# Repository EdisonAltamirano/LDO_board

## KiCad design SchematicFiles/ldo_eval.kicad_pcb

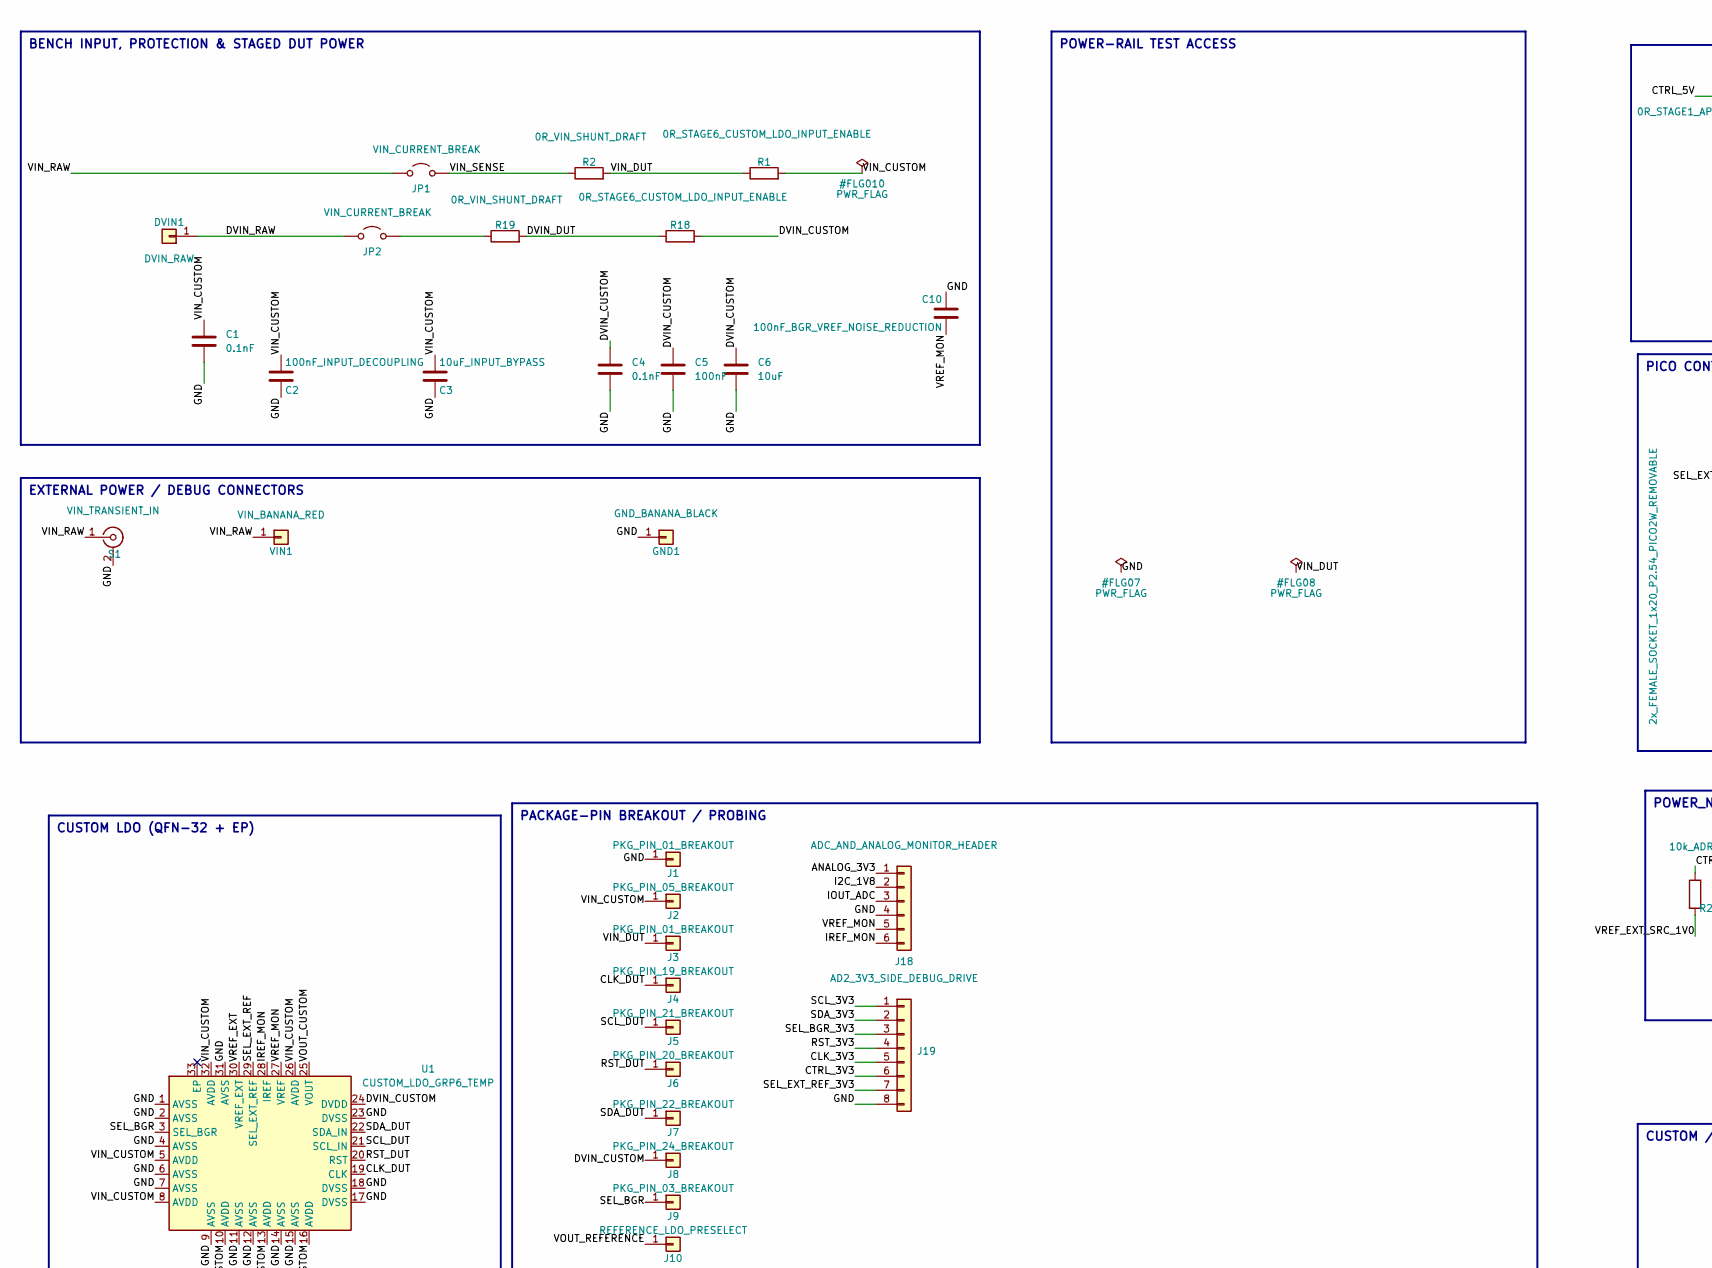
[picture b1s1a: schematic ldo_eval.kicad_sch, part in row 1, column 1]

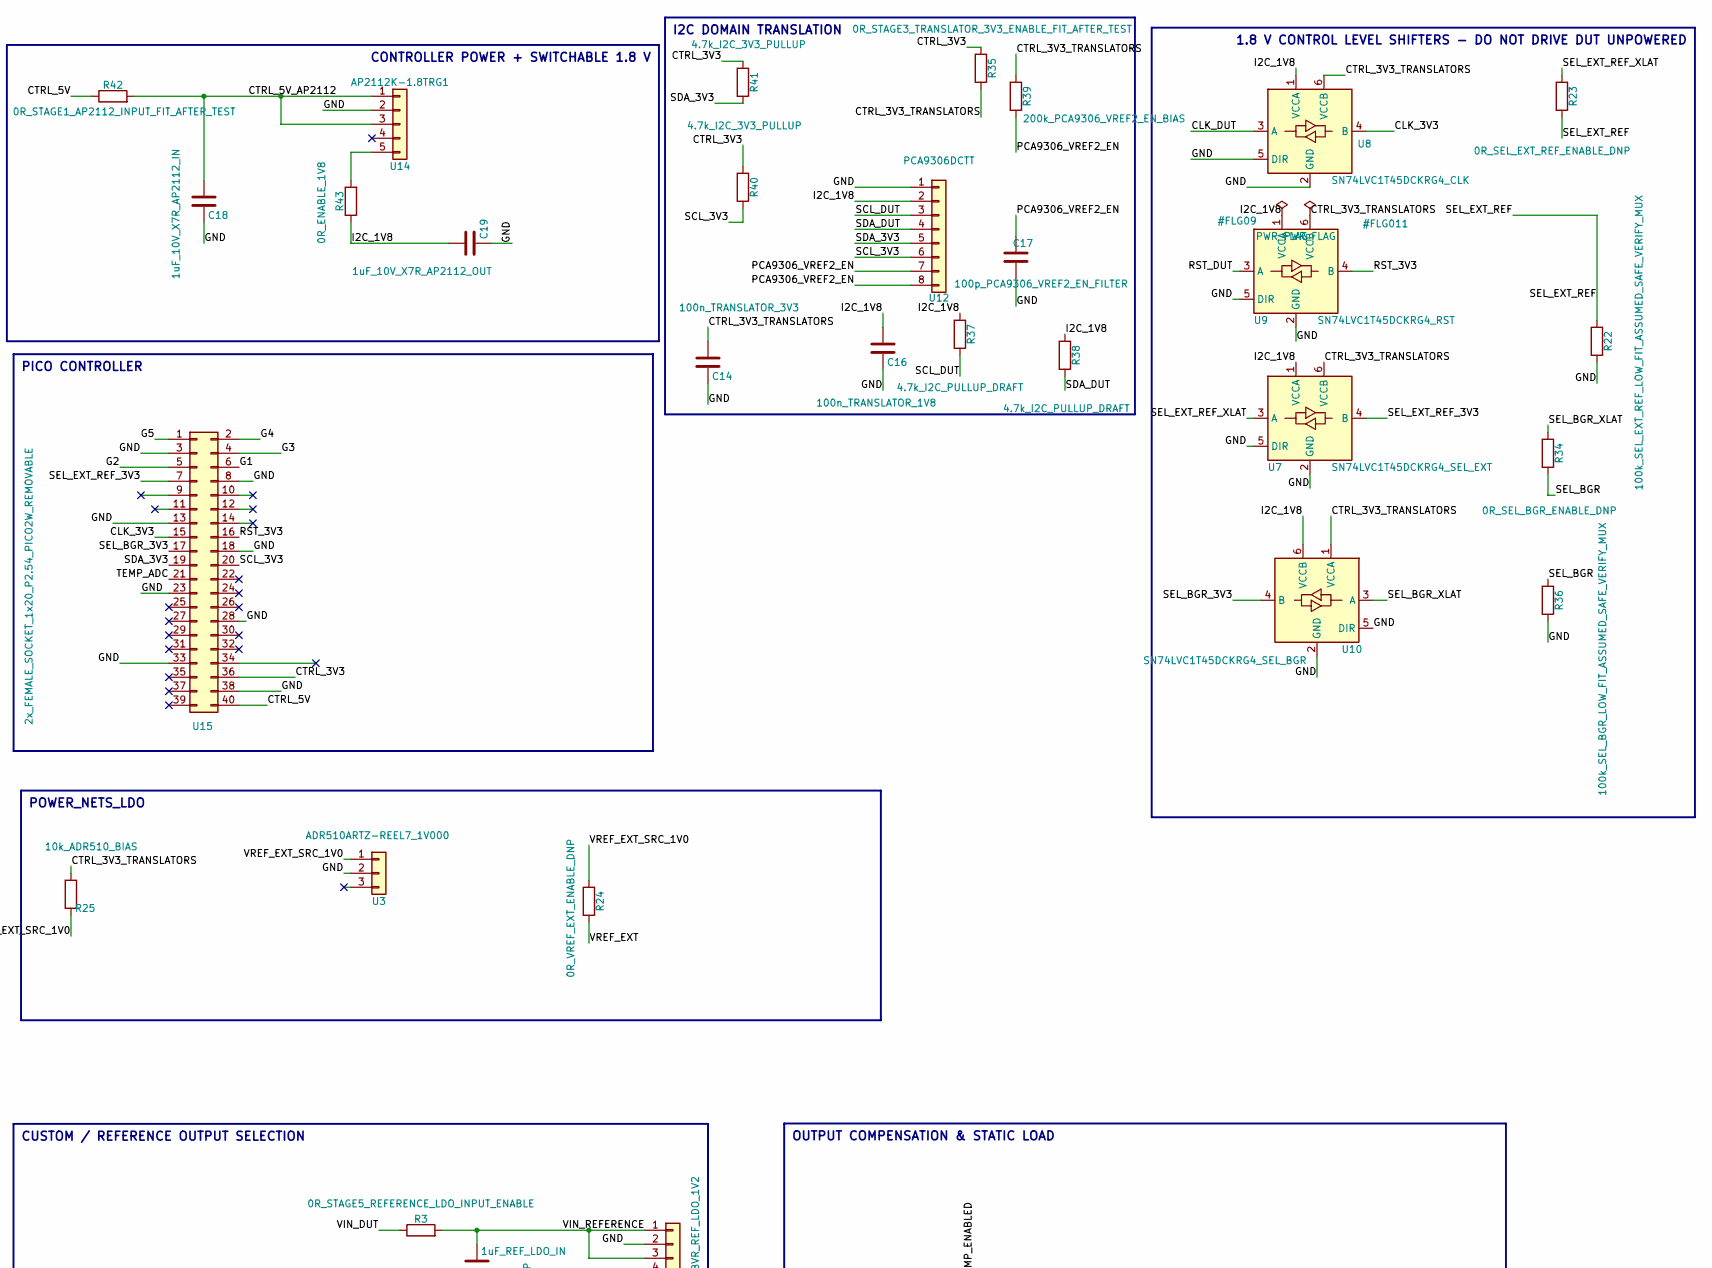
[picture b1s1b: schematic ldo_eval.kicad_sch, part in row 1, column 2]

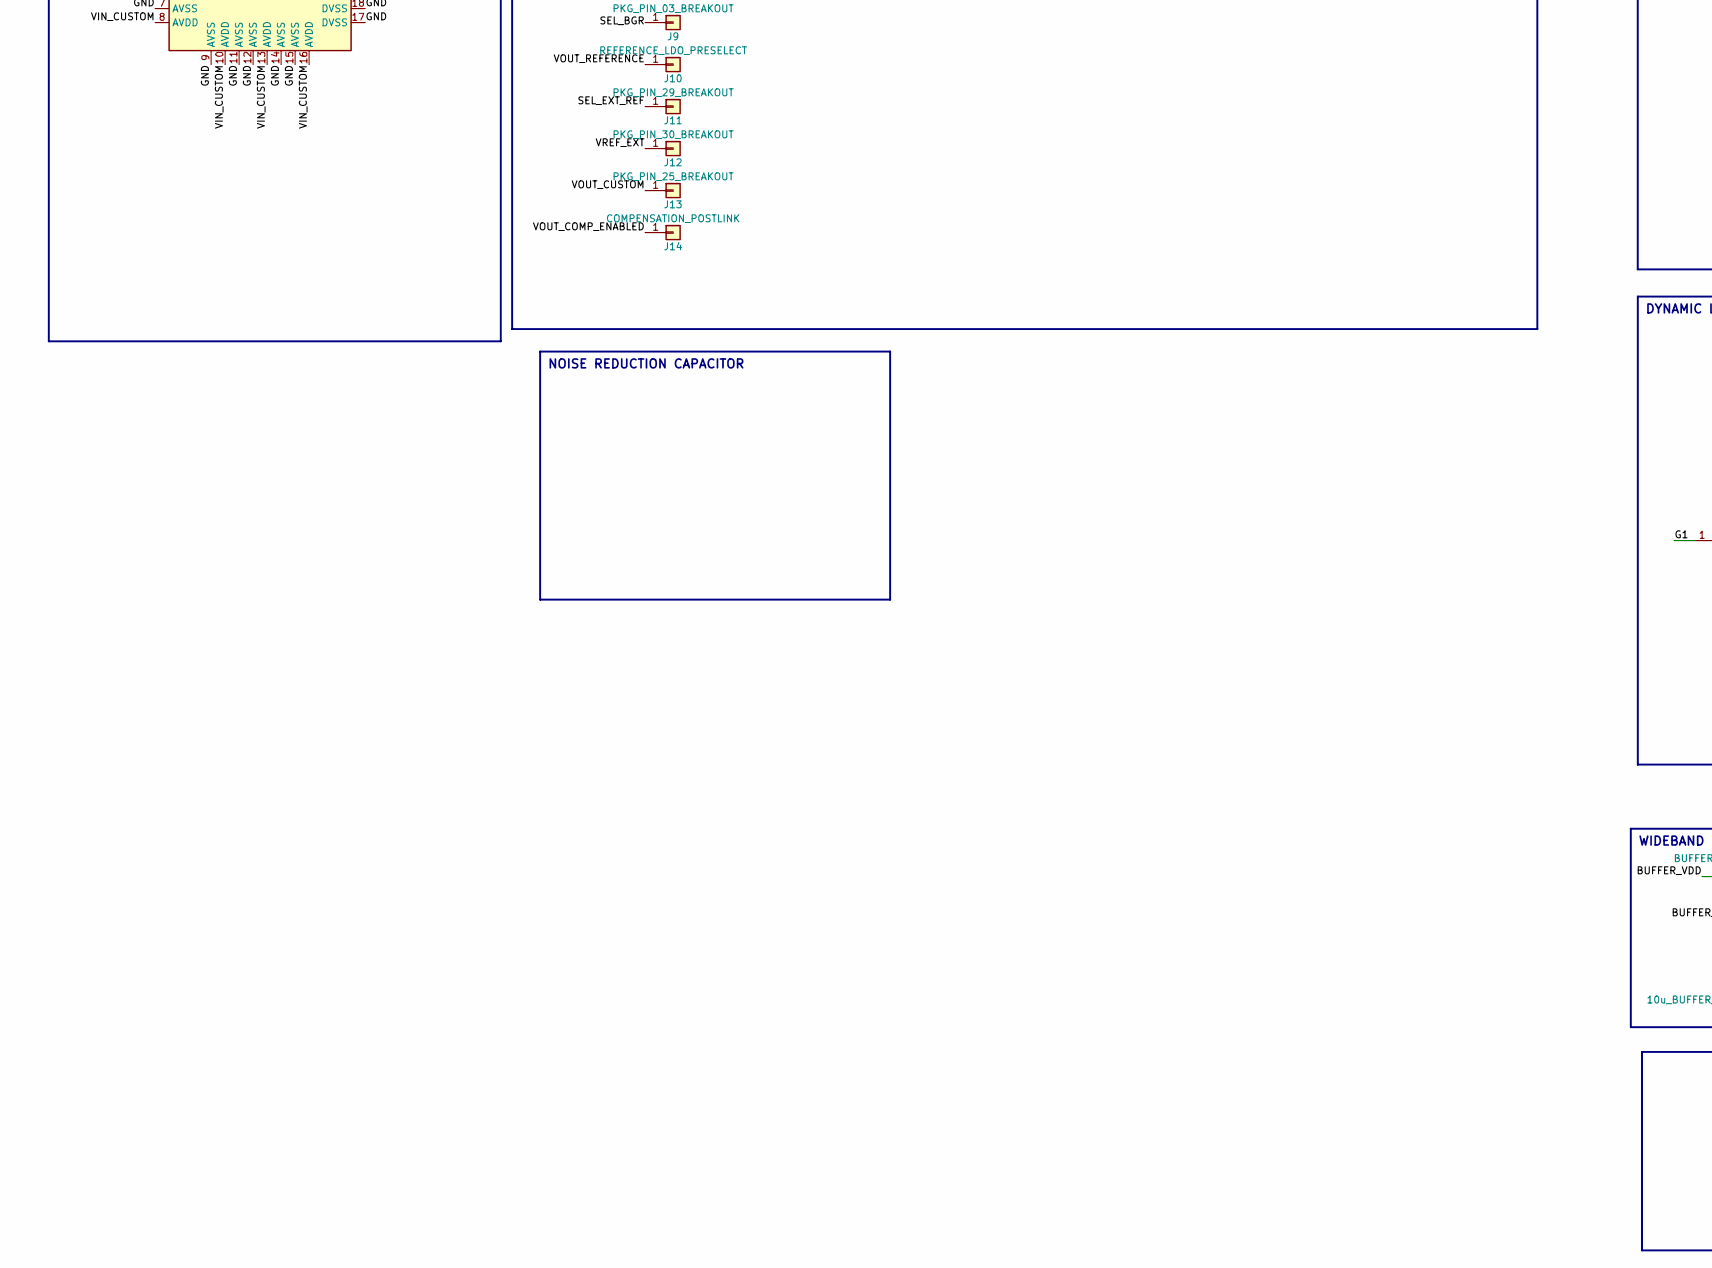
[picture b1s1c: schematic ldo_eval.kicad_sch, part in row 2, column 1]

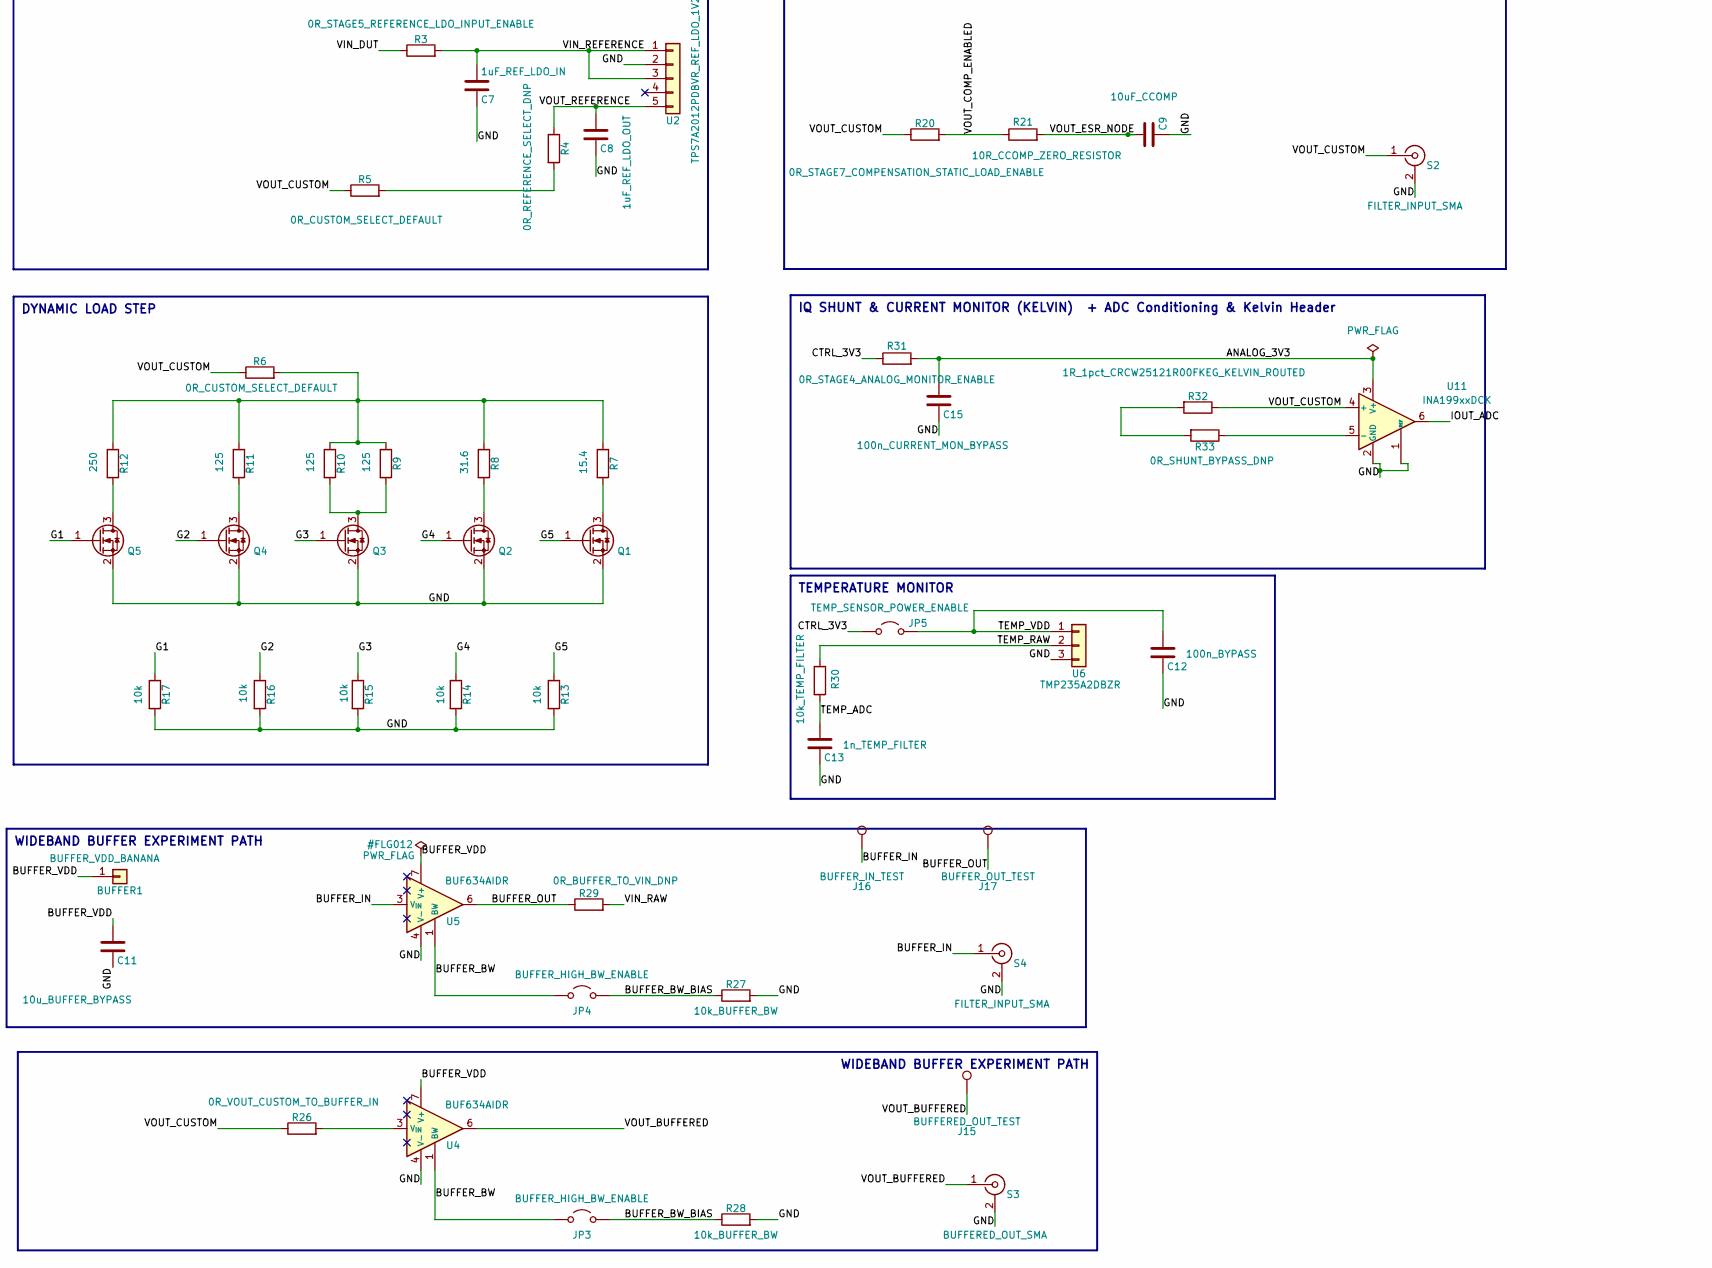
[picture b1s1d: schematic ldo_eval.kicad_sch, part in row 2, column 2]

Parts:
BUFFER1: BUFFER_VDD_BANANA; CalTest_CT3151
C1, C4: 0.1nF; C_0805_2012Metric; Manufacturer Part Number C0805C101K8RACTU
C2: 100nF_INPUT_DECOUPLING; C_0805_2012Metric
C3: 10uF_INPUT_BYPASS; C_0805_2012Metric
C5: 100nF; C_0805_2012Metric; Manufacturer Part Number C0805C104K8RACTU
C6: 10uF; C_0805_2012Metric; Manufacturer Part Number C0805C106K8RACTU
C7: 1uF_REF_LDO_IN; C_0603_1608Metric
C8: 1uF_REF_LDO_OUT; C_0603_1608Metric
C9: 10uF_CCOMP; C_0805_2012Metric
C10: 100nF_BGR_VREF_NOISE_REDUCTION; C_0603_1608Metric
C11: 10u_BUFFER_BYPASS; C_0805_2012Metric
C12: 100n_BYPASS; C_0805_2012Metric
C13: 1n_TEMP_FILTER; C_0805_2012Metric
C14: 100n_TRANSLATOR_3V3; C_0603_1608Metric
C15: 100n_CURRENT_MON_BYPASS; C_0603_1608Metric
C16: 100n_TRANSLATOR_1V8; C_0603_1608Metric
C17: 100p_PCA9306_VREF2_EN_FILTER; C_0603_1608Metric
C18: 1uF_10V_X7R_AP2112_IN; C_0805_2012Metric
C19: 1uF_10V_X7R_AP2112_OUT; C_0805_2012Metric
DVIN1: DVIN_RAW; CalTest_CT3151
GND1: GND_BANANA_BLACK; CalTest_CT3151
J1, J3: PKG_PIN_01_BREAKOUT; PinHeader_1x01_P2.54mm_Vertical
J2: PKG_PIN_05_BREAKOUT; PinHeader_1x01_P2.54mm_Vertical
J4: PKG_PIN_19_BREAKOUT; PinHeader_1x01_P2.54mm_Vertical
J5: PKG_PIN_21_BREAKOUT; PinHeader_1x01_P2.54mm_Vertical
J6: PKG_PIN_20_BREAKOUT; PinHeader_1x01_P2.54mm_Vertical
J7: PKG_PIN_22_BREAKOUT; PinHeader_1x01_P2.54mm_Vertical
J8: PKG_PIN_24_BREAKOUT; PinHeader_1x01_P2.54mm_Vertical
J9: PKG_PIN_03_BREAKOUT; PinHeader_1x01_P2.54mm_Vertical
J10: REFERENCE_LDO_PRESELECT; PinHeader_1x01_P2.54mm_Vertical
J11: PKG_PIN_29_BREAKOUT; PinHeader_1x01_P2.54mm_Vertical
J12: PKG_PIN_30_BREAKOUT; PinHeader_1x01_P2.54mm_Vertical
J13: PKG_PIN_25_BREAKOUT; PinHeader_1x01_P2.54mm_Vertical
J14: COMPENSATION_POSTLINK; PinHeader_1x01_P2.54mm_Vertical
J15: BUFFERED_OUT_TEST; PinHeader_1x01_P2.54mm_Vertical
J16: BUFFER_IN_TEST; PinHeader_1x01_P2.54mm_Vertical
J17: BUFFER_OUT_TEST; PinHeader_1x01_P2.54mm_Vertical
J18: ADC_AND_ANALOG_MONITOR_HEADER; PinHeader_1x06_P2.54mm_Vertical
J19: AD2_3V3_SIDE_DEBUG_DRIVE; PinHeader_1x08_P2.54mm_Vertical
JP1, JP2: VIN_CURRENT_BREAK; PinHeader_1x02_P2.54mm_Vertical
JP3, JP4: BUFFER_HIGH_BW_ENABLE; PinHeader_1x02_P2.54mm_Vertical
JP5: TEMP_SENSOR_POWER_ENABLE; PinHeader_1x02_P2.54mm_Vertical
Q1, Q2, Q3, Q4, Q5: FDV305N:SOT95P240X111; SOT-23
R1, R18: 0R_STAGE6_CUSTOM_LDO_INPUT_ENABLE; R_0805_2012Metric
R2, R19: 0R_VIN_SHUNT_DRAFT; R_2512_6332Metric
R3: 0R_STAGE5_REFERENCE_LDO_INPUT_ENABLE; R_0805_2012Metric
R4: 0R_REFERENCE_SELECT_DNP; R_0805_2012Metric
R5, R6: 0R_CUSTOM_SELECT_DEFAULT; R_0805_2012Metric
R7: 15.4; R_0805_2012Metric_Pad1.20x1.40mm_HandSolder
R8: 31.6; R_0805_2012Metric_Pad1.20x1.40mm_HandSolder
R9, R10, R11: 125; R_0805_2012Metric_Pad1.20x1.40mm_HandSolder
R12: 250; R_0805_2012Metric_Pad1.20x1.40mm_HandSolder
R13, R14, R15, R16, R17: 10k; R_0603_1608Metric
R20: 0R_STAGE7_COMPENSATION_STATIC_LOAD_ENABLE; R_0805_2012Metric
R21: 10R_CCOMP_ZERO_RESISTOR; R_0805_2012Metric
R22: 100k_SEL_EXT_REF_LOW_FIT_ASSUMED_SAFE_VERIFY_MUX; R_0603_1608Metric
R23: 0R_SEL_EXT_REF_ENABLE_DNP; R_0603_1608Metric
R24: 0R_VREF_EXT_ENABLE_DNP; R_0603_1608Metric
R25: 10k_ADR510_BIAS; R_0603_1608Metric
R26: 0R_VOUT_CUSTOM_TO_BUFFER_IN; R_0805_2012Metric
R27, R28: 10k_BUFFER_BW; R_0805_2012Metric
R29: 0R_BUFFER_TO_VIN_DNP; R_0805_2012Metric
R30: 10k_TEMP_FILTER; R_0805_2012Metric
R31: 0R_STAGE4_ANALOG_MONITOR_ENABLE; R_0805_2012Metric
R32: 1R_1pct_CRCW25121R00FKEG_KELVIN_ROUTED; R_2512_6332Metric
R33: 0R_SHUNT_BYPASS_DNP; R_0805_2012Metric
R34: 0R_SEL_BGR_ENABLE_DNP; R_0603_1608Metric
R35: 0R_STAGE3_TRANSLATOR_3V3_ENABLE_FIT_AFTER_TEST; R_0805_2012Metric
R36: 100k_SEL_BGR_LOW_FIT_ASSUMED_SAFE_VERIFY_MUX; R_0603_1608Metric
R37, R38: 4.7k_I2C_PULLUP_DRAFT; R_0603_1608Metric
R39: 200k_PCA9306_VREF2_EN_BIAS; R_0603_1608Metric
R40, R41: 4.7k_I2C_3V3_PULLUP; R_0603_1608Metric
R42: 0R_STAGE1_AP2112_INPUT_FIT_AFTER_TEST; R_0805_2012Metric
R43: 0R_ENABLE_1V8; R_0805_2012Metric
S1: VIN_TRANSIENT_IN; SMA_Amphenol_132134_Vertical
S2, S4: FILTER_INPUT_SMA; SMA_Amphenol_132134_Vertical
S3: BUFFERED_OUT_SMA; SMA_Amphenol_132134_Vertical
U1: CUSTOM_LDO_GRP6_TEMP; QFN32_7x7_P0.65_TEMP
U2: TPS7A2012PDBVR_REF_LDO_1V2; SOT-23-5
U3: ADR510ARTZ-REEL7_1V000; SOT-23
U4, U5: BUF634AIDR; SOIC-8_3.9x4.9mm_P1.27mm
U6: TMP235A2DBZR; SOT-23
U7: SN74LVC1T45DCKRG4_SEL_EXT; SOT-363_SC-70-6
U8: SN74LVC1T45DCKRG4_CLK; SOT-363_SC-70-6
U9: SN74LVC1T45DCKRG4_RST; SOT-363_SC-70-6
U10: SN74LVC1T45DCKRG4_SEL_BGR; SOT-363_SC-70-6
U11: INA199xxDCK; SOT-363_SC-70-6
U12: PCA9306DCTT; SSOP-8_2.95x2.8mm_P0.65mm
U14: AP2112K-1.8TRG1; SOT-23-5
U15: 2x_FEMALE_SOCKET_1x20_P2.54_PICO2W_REMOVABLE; Pico_2W_Dual_1x20_Female_Sockets
VIN1: VIN_BANANA_RED; CalTest_CT3151

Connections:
/ANALOG_3V3: C15.1, J18.1, R31.2, U11.3 (V+)
/BUFFER_BW: JP3.1 (A), JP4.1 (A), U4.1 (BW), U5.1 (BW)
/BUFFER_BW_BIAS: JP3.2 (B), JP4.2 (B), R27.1, R28.1
/BUFFER_IN: J16.1 (1_1), S4.1 (In), U5.3 (V_{IN})
/BUFFER_OUT: J17.1 (1_1), R29.1, U5.6
/BUFFER_VDD: BUFFER1.1 (Pin_1_1), C11.1, U4.7 (V+), U5.7 (V+)
/CLK_3V3: J19.5, U8.4 (B), U15.15
/CLK_DUT: J4.1 (Pin_1_1), U1.19 (CLK), U8.3 (A)
/CTRL_3V3: J19.6, JP5.1 (A), R31.1, R35.1, R40.1, R41.1, U15.36
/CTRL_3V3_TRANSLATORS: C14.1, R25.1, R35.2, R39.1, U7.6 (VCCB), U8.6 (VCCB), U9.6 (VCCB), U10.1 (VCCA)
/CTRL_5V: R42.1, U15.40
/CTRL_5V_AP2112: C18.1, R42.2, U14.1, U14.3
/DVIN_CUSTOM: C4.1, C5.1, C6.1, J8.1 (Pin_1_1), R18.2, U1.24 (DVDD)
/DVIN_DUT: R18.1, R19.2
/DVIN_RAW: DVIN1.1 (Pin_1_1), JP2.1 (A)
/G1: Q5.1 (G), R17.1, U15.6
/G2: Q4.1 (G), R16.1, U15.5
/G3: Q3.1 (G), R15.1, U15.4
/G4: Q2.1 (G), R14.1, U15.2
/G5: Q1.1 (G), R13.1, U15.1
/GND: C1.2, C2.2, C3.2, C4.2, C5.2, C6.2, C7.2, C8.2, C9.2, C10.2, C11.2, C12.2, C13.2, C14.2, C15.2, C16.2, C17.2, C18.2, C19.2, GND1.1 (Pin_1_1), J1.1 (Pin_1_1), J18.4, J19.8, Q1.2 (S), Q2.2 (S), Q3.2 (S), Q4.2 (S), Q5.2 (S), R13.2, R14.2, R15.2, R16.2, R17.2, R22.2, R27.2, R28.2, R36.2, S1.2 (Ext), S2.2 (Ext), S3.2 (Ext), S4.2 (Ext), U1.1 (AVSS), U1.2 (AVSS), U1.4 (AVSS), U1.6 (AVSS), U1.7 (AVSS), U1.9 (AVSS), U1.11 (AVSS), U1.12 (AVSS), U1.14 (AVSS), U1.15 (AVSS), U1.17 (DVSS), U1.18 (DVSS), U1.23 (DVSS), U1.31 (AVSS), U2.2, U3.2, U4.4 (V-), U5.4 (V-), U6.3, U7.2 (GND), U7.5 (DIR), U8.2 (GND), U8.5 (DIR), U9.2 (GND), U9.5 (DIR), U10.2 (GND), U10.5 (DIR), U11.1 (REF), U11.2 (GND), U12.1, U14.2, U15.3, U15.8, U15.13, U15.18, U15.23, U15.28, U15.33, U15.38
/I2C_1V8: C16.1, C19.1, J18.2, R37.1, R38.1, R43.1, U7.1 (VCCA), U8.1 (VCCA), U9.1 (VCCA), U10.6 (VCCB), U12.2
/IOUT_ADC: J18.3, U11.6
/IREF_MON: J18.6, U1.28 (IREF)
/PCA9306_VREF2_EN: C17.1, R39.2, U12.7, U12.8
/RST_3V3: J19.4, U9.4 (B), U15.16
/RST_DUT: J6.1 (Pin_1_1), U1.20 (RST), U9.3 (A)
/SCL_3V3: J19.1, R40.2, U12.6, U15.20
/SCL_DUT: J5.1 (Pin_1_1), R37.2, U1.21 (SCL_IN), U12.3
/SDA_3V3: J19.2, R41.2, U12.5, U15.19
/SDA_DUT: J7.1 (Pin_1_1), R38.2, U1.22 (SDA_IN), U12.4
/SEL_BGR: J9.1 (Pin_1_1), R34.2, R36.1, U1.3 (SEL_BGR)
/SEL_BGR_3V3: J19.3, U10.4 (B), U15.17
/SEL_BGR_XLAT: R34.1, U10.3 (A)
/SEL_EXT_REF: J11.1 (Pin_1_1), R22.1, R23.2, U1.29 (SEL_EXT_REF)
/SEL_EXT_REF_3V3: J19.7, U7.4 (B), U15.7
/SEL_EXT_REF_XLAT: R23.1, U7.3 (A)
/TEMP_ADC: C13.1, R30.2, U15.21
/TEMP_RAW: R30.1, U6.2
/TEMP_VDD: C12.1, JP5.2 (B), U6.1
/VIN_CUSTOM: C1.1, C2.1, C3.1, J2.1 (Pin_1_1), R1.2, U1.5 (AVDD), U1.8 (AVDD), U1.10 (AVDD), U1.13 (AVDD), U1.16 (AVDD), U1.26 (AVDD), U1.32 (AVDD)
/VIN_DUT: J3.1 (Pin_1_1), R1.1, R2.2, R3.1
/VIN_RAW: JP1.1 (A), R29.2, S1.1 (In), VIN1.1 (Pin_1_1)
/VIN_REFERENCE: C7.1, R3.2, U2.1, U2.3
/VIN_SENSE: JP1.2 (B), R2.1
/VOUT_BUFFERED: J15.1 (1_1), S3.1 (In), U4.6
/VOUT_COMP_ENABLED: J14.1 (Pin_1_1), R20.2, R21.1
/VOUT_CUSTOM: J13.1 (Pin_1_1), R5.1, R6.1, R20.1, R26.1, R32.1, S2.1 (In), U1.25 (VOUT), U11.4 (+)
/VOUT_ESR_NODE: C9.1, R21.2
/VOUT_REFERENCE: C8.1, J10.1 (Pin_1_1), R4.1, U2.5
/VREF_EXT: J12.1 (Pin_1_1), R24.2, U1.30 (VREF_EXT)
/VREF_EXT_SRC_1V0: R24.1, R25.2, U3.1
/VREF_MON: C10.1, J18.5, U1.27 (VREF)
unnamed: JP2.2 (B), R19.1
unnamed: Q1.3 (D), R7.2
unnamed: Q2.3 (D), R8.2
unnamed: Q3.3 (D), R9.2, R10.2
unnamed: Q4.3 (D), R11.2
unnamed: Q5.3 (D), R12.2
unnamed: R4.2, R5.2
unnamed: R6.2, R7.1, R8.1, R9.1, R10.1, R11.1, R12.1
unnamed: R32.2, R33.2
unnamed: R26.2, U4.3 (V_{IN})
unnamed: R33.1, U11.5 (-)
unnamed: R43.2, U14.5

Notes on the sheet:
PICO CONTROLLER
WIDEBAND BUFFER EXPERIMENT PATH
DYNAMIC LOAD STEP
CUSTOM LDO (QFN-32 + EP)
CUSTOM / REFERENCE OUTPUT SELECTION
POWER_NETS_LDO
NOISE REDUCTION CAPACITOR
POWER-RAIL TEST ACCESS
CONTROLLER POWER + SWITCHABLE 1.8 V
TEMPERATURE MONITOR
I2C DOMAIN TRANSLATION
1.8 V CONTROL LEVEL SHIFTERS - DO NOT DRIVE DUT UNPOWERED
BENCH INPUT, PROTECTION & STAGED DUT POWER
OUTPUT COMPENSATION & STATIC LOAD
IQ SHUNT & CURRENT MONITOR (KELVIN) + ADC Conditioning & Kelvin Header
PACKAGE-PIN BREAKOUT / PROBING
EXTERNAL POWER / DEBUG CONNECTORS

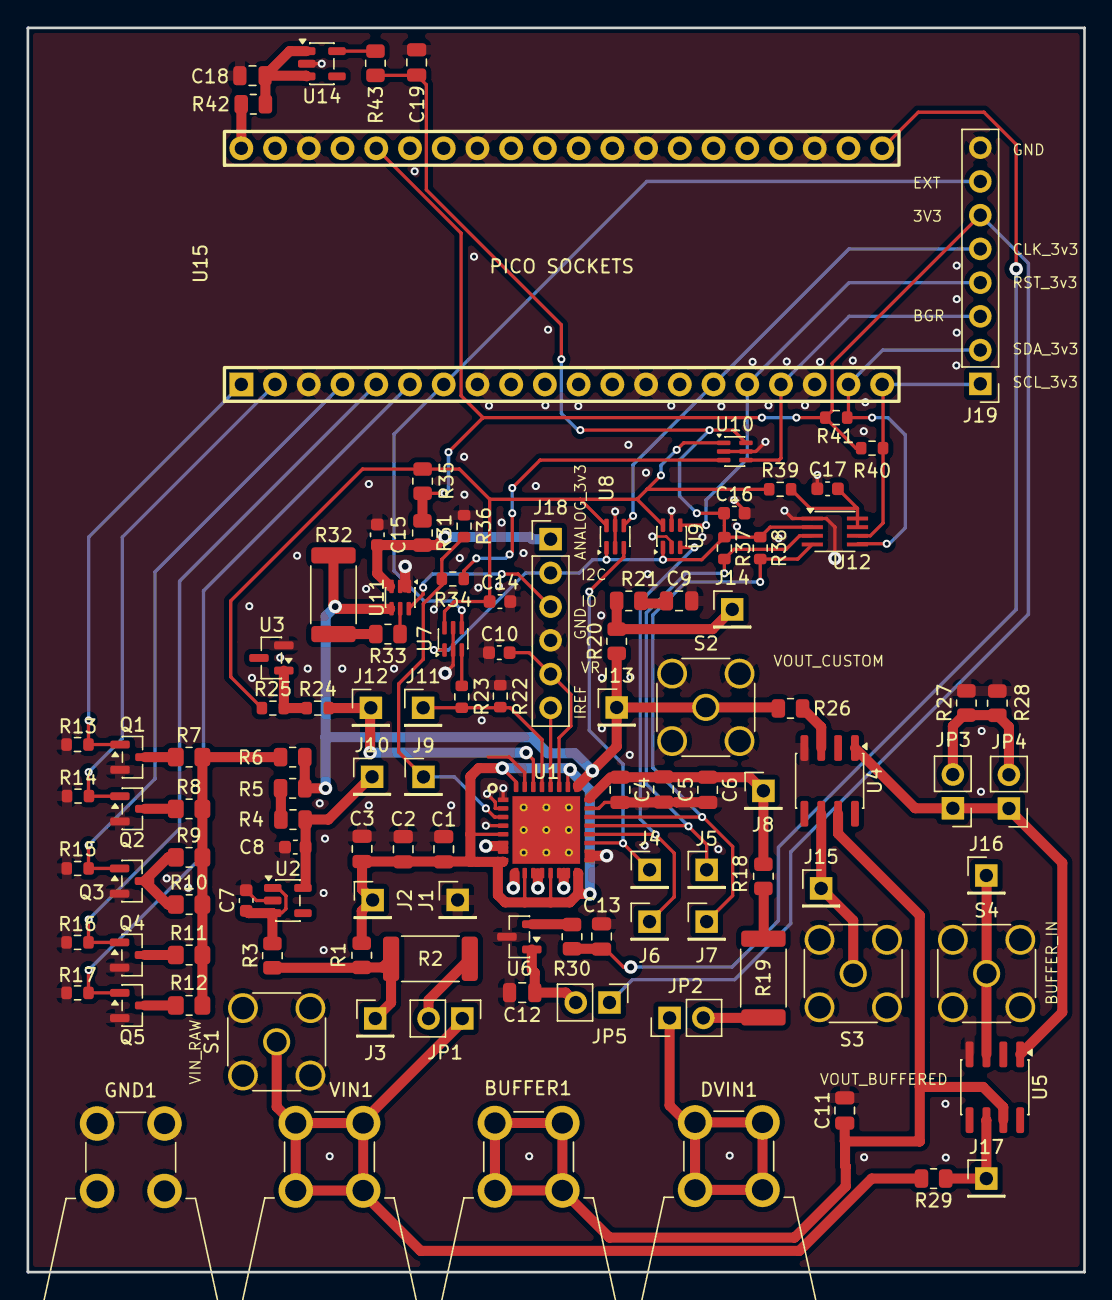
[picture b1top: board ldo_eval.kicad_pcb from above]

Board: 4 copper layers, 79.6 x 93.7 mm, 113 parts (0 on the bottom side), 65 nets.

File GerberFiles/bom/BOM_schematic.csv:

"References","Value","Footprint","Quantity","DNP"
"BUFFER1","BUFFER_VDD_BANANA","Connector:CalTest_CT3151","1",""
"C1,C4","0.1nF","Capacitor_SMD:C_0805_2012Metric","2",""
"C2","100nF_INPUT_DECOUPLING","Capacitor_SMD:C_0805_2012Metric","1",""
"C3","10uF_INPUT_BYPASS","Capacitor_SMD:C_0805_2012Metric","1",""
"C5","100nF","Capacitor_SMD:C_0805_2012Metric","1",""
"C6","10uF","Capacitor_SMD:C_0805_2012Metric","1",""
"C7","1uF_REF_LDO_IN","Capacitor_SMD:C_0603_1608Metric","1",""
"C8","1uF_REF_LDO_OUT","Capacitor_SMD:C_0603_1608Metric","1",""
"C9","10uF_CCOMP","Capacitor_SMD:C_0805_2012Metric","1",""
"C10","100nF_BGR_VREF_NOISE_REDUCTION","Capacitor_SMD:C_0603_1608Metric","1",""
"C11","10u_BUFFER_BYPASS","Capacitor_SMD:C_0805_2012Metric","1",""
"C12","100n_BYPASS","Capacitor_SMD:C_0805_2012Metric","1",""
"C13","1n_TEMP_FILTER","Capacitor_SMD:C_0805_2012Metric","1",""
"C14","100n_TRANSLATOR_3V3","Capacitor_SMD:C_0603_1608Metric","1",""
"C15","100n_CURRENT_MON_BYPASS","Capacitor_SMD:C_0603_1608Metric","1",""
"C16","100n_TRANSLATOR_1V8","Capacitor_SMD:C_0603_1608Metric","1",""
"C17","100p_PCA9306_VREF2_EN_FILTER","Capacitor_SMD:C_0603_1608Metric","1",""
"C18","1uF_10V_X7R_AP2112_IN","Capacitor_SMD:C_0805_2012Metric","1",""
"C19","1uF_10V_X7R_AP2112_OUT","Capacitor_SMD:C_0805_2012Metric","1",""
"DVIN1","DVIN_RAW","Connector:CalTest_CT3151","1",""
"GND1","GND_BANANA_BLACK","Connector:CalTest_CT3151","1",""
"J1,J3","PKG_PIN_01_BREAKOUT","Connector_PinHeader_2.54mm:PinHeader_1x01_P2.54mm_Vertical","2",""
"J2","PKG_PIN_05_BREAKOUT","Connector_PinHeader_2.54mm:PinHeader_1x01_P2.54mm_Vertical","1",""
"J4","PKG_PIN_19_BREAKOUT","Connector_PinHeader_2.54mm:PinHeader_1x01_P2.54mm_Vertical","1",""
"J5","PKG_PIN_21_BREAKOUT","Connector_PinHeader_2.54mm:PinHeader_1x01_P2.54mm_Vertical","1",""
"J6","PKG_PIN_20_BREAKOUT","Connector_PinHeader_2.54mm:PinHeader_1x01_P2.54mm_Vertical","1",""
"J7","PKG_PIN_22_BREAKOUT","Connector_PinHeader_2.54mm:PinHeader_1x01_P2.54mm_Vertical","1",""
"J8","PKG_PIN_24_BREAKOUT","Connector_PinHeader_2.54mm:PinHeader_1x01_P2.54mm_Vertical","1",""
"J9","PKG_PIN_03_BREAKOUT","Connector_PinHeader_2.54mm:PinHeader_1x01_P2.54mm_Vertical","1",""
"J10","REFERENCE_LDO_PRESELECT","Connector_PinHeader_2.54mm:PinHeader_1x01_P2.54mm_Vertical","1",""
"J11","PKG_PIN_29_BREAKOUT","Connector_PinHeader_2.54mm:PinHeader_1x01_P2.54mm_Vertical","1",""
"J12","PKG_PIN_30_BREAKOUT","Connector_PinHeader_2.54mm:PinHeader_1x01_P2.54mm_Vertical","1",""
"J13","PKG_PIN_25_BREAKOUT","Connector_PinHeader_2.54mm:PinHeader_1x01_P2.54mm_Vertical","1",""
"J14","COMPENSATION_POSTLINK","Connector_PinHeader_2.54mm:PinHeader_1x01_P2.54mm_Vertical","1",""
"J15","BUFFERED_OUT_TEST","Connector_PinHeader_2.54mm:PinHeader_1x01_P2.54mm_Vertical","1",""
"J16","BUFFER_IN_TEST","Connector_PinHeader_2.54mm:PinHeader_1x01_P2.54mm_Vertical","1",""
"J17","BUFFER_OUT_TEST","Connector_PinHeader_2.54mm:PinHeader_1x01_P2.54mm_Vertical","1",""
"J18","ADC_AND_ANALOG_MONITOR_HEADER","Connector_PinHeader_2.54mm:PinHeader_1x06_P2.54mm_Vertical","1",""
"J19","AD2_3V3_SIDE_DEBUG_DRIVE","Connector_PinHeader_2.54mm:PinHeader_1x08_P2.54mm_Vertical","1",""
"JP1,JP2","VIN_CURRENT_BREAK","Connector_PinHeader_2.54mm:PinHeader_1x02_P2.54mm_Vertical","2",""
"JP3,JP4","BUFFER_HIGH_BW_ENABLE","Connector_PinHeader_2.54mm:PinHeader_1x02_P2.54mm_Vertical","2",""
"JP5","TEMP_SENSOR_POWER_ENABLE","Connector_PinHeader_2.54mm:PinHeader_1x02_P2.54mm_Vertical","1",""
"Q1-Q5","FDV305N:SOT95P240X111","Package_TO_SOT_SMD:SOT-23","5",""
"R1,R18","0R_STAGE6_CUSTOM_LDO_INPUT_ENABLE","Resistor_SMD:R_0805_2012Metric","2",""
"R2,R19","0R_VIN_SHUNT_DRAFT","Resistor_SMD:R_2512_6332Metric","2",""
"R3","0R_STAGE5_REFERENCE_LDO_INPUT_ENABLE","Resistor_SMD:R_0805_2012Metric","1",""
"R4","0R_REFERENCE_SELECT_DNP","Resistor_SMD:R_0805_2012Metric","1",""
"R5,R6","0R_CUSTOM_SELECT_DEFAULT","Resistor_SMD:R_0805_2012Metric","2",""
"R7","15.4","Resistor_SMD:R_0805_2012Metric_Pad1.20x1.40mm_HandSolder","1",""
"R8","31.6","Resistor_SMD:R_0805_2012Metric_Pad1.20x1.40mm_HandSolder","1",""
"R9-R11","125","Resistor_SMD:R_0805_2012Metric_Pad1.20x1.40mm_HandSolder","3",""
"R12","250","Resistor_SMD:R_0805_2012Metric_Pad1.20x1.40mm_HandSolder","1",""
"R13-R17","10k","Resistor_SMD:R_0603_1608Metric","5",""
"R20","0R_STAGE7_COMPENSATION_STATIC_LOAD_ENABLE","Resistor_SMD:R_0805_2012Metric","1",""
"R21","10R_CCOMP_ZERO_RESISTOR","Resistor_SMD:R_0805_2012Metric","1",""
"R22","100k_SEL_EXT_REF_LOW_FIT_ASSUMED_SAFE_VERIFY_MUX","Resistor_SMD:R_0603_1608Metric","1",""
"R23","0R_SEL_EXT_REF_ENABLE_DNP","Resistor_SMD:R_0603_1608Metric","1",""
"R24","0R_VREF_EXT_ENABLE_DNP","Resistor_SMD:R_0603_1608Metric","1",""
"R25","10k_ADR510_BIAS","Resistor_SMD:R_0603_1608Metric","1",""
"R26","0R_VOUT_CUSTOM_TO_BUFFER_IN","Resistor_SMD:R_0805_2012Metric","1",""
"R27,R28","10k_BUFFER_BW","Resistor_SMD:R_0805_2012Metric","2",""
"R29","0R_BUFFER_TO_VIN_DNP","Resistor_SMD:R_0805_2012Metric","1",""
"R30","10k_TEMP_FILTER","Resistor_SMD:R_0805_2012Metric","1",""
"R31","0R_STAGE4_ANALOG_MONITOR_ENABLE","Resistor_SMD:R_0805_2012Metric","1",""
"R32","1R_1pct_CRCW25121R00FKEG_KELVIN_ROUTED","Resistor_SMD:R_2512_6332Metric","1",""
"R33","0R_SHUNT_BYPASS_DNP","Resistor_SMD:R_0805_2012Metric","1",""
"R34","0R_SEL_BGR_ENABLE_DNP","Resistor_SMD:R_0603_1608Metric","1",""
"R35","0R_STAGE3_TRANSLATOR_3V3_ENABLE_FIT_AFTER_TEST","Resistor_SMD:R_0805_2012Metric","1",""
"R36","100k_SEL_BGR_LOW_FIT_ASSUMED_SAFE_VERIFY_MUX","Resistor_SMD:R_0603_1608Metric","1",""
"R37,R38","4.7k_I2C_PULLUP_DRAFT","Resistor_SMD:R_0603_1608Metric","2",""
"R39","200k_PCA9306_VREF2_EN_BIAS","Resistor_SMD:R_0603_1608Metric","1",""
"R40,R41","4.7k_I2C_3V3_PULLUP","Resistor_SMD:R_0603_1608Metric","2",""
"R42","0R_STAGE1_AP2112_INPUT_FIT_AFTER_TEST","Resistor_SMD:R_0805_2012Metric","1",""
"R43","0R_ENABLE_1V8","Resistor_SMD:R_0805_2012Metric","1",""
"S1","VIN_TRANSIENT_IN","Connector_Coaxial:SMA_Amphenol_132134_Vertical","1",""
"S2,S4","FILTER_INPUT_SMA","Connector_Coaxial:SMA_Amphenol_132134_Vertical","2",""
"S3","BUFFERED_OUT_SMA","Connector_Coaxial:SMA_Amphenol_132134_Vertical","1",""
"U1","CUSTOM_LDO_GRP6_TEMP","custom_footprints:QFN32_7x7_P0.65_TEMP","1",""
"U2","TPS7A2012PDBVR_REF_LDO_1V2","Package_TO_SOT_SMD:SOT-23-5","1",""
"U3","ADR510ARTZ-REEL7_1V000","Package_TO_SOT_SMD:SOT-23","1",""
"U4,U5","BUF634AIDR","Package_SO:SOIC-8_3.9x4.9mm_P1.27mm","2",""
"U6","TMP235A2DBZR","Package_TO_SOT_SMD:SOT-23","1",""
"U7","SN74LVC1T45DCKRG4_SEL_EXT","Package_TO_SOT_SMD:SOT-363_SC-70-6","1",""
"U8","SN74LVC1T45DCKRG4_CLK","Package_TO_SOT_SMD:SOT-363_SC-70-6","1",""
"U9","SN74LVC1T45DCKRG4_RST","Package_TO_SOT_SMD:SOT-363_SC-70-6","1",""
"U10","SN74LVC1T45DCKRG4_SEL_BGR","Package_TO_SOT_SMD:SOT-363_SC-70-6","1",""
"U11","INA199xxDCK","Package_TO_SOT_SMD:SOT-363_SC-70-6","1",""
"U12","PCA9306DCTT","Package_SO:SSOP-8_2.95x2.8mm_P0.65mm","1",""
"U14","AP2112K-1.8TRG1","Package_TO_SOT_SMD:SOT-23-5","1",""
"U15","2x_FEMALE_SOCKET_1x20_P2.54_PICO2W_REMOVABLE","custom_footprints:Pico_2W_Dual_1x20_Female_Sockets","1",""
"VIN1","VIN_BANANA_RED","Connector:CalTest_CT3151","1",""
